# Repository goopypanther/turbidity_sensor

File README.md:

Water Turbidity Sensor Project
==============================

Hackerbot labs would like to place a number of water turbidity sensor packages in dive sites around Puget Sound to provide up-to-date visibility and water temperature information.

The sensor string will be suspended between a weight and small buoy which will contain a battery, solar panels and communication antenna. The installations will be close to shore and will probably use local wifi or a LTE cellular data connection.

Research
--------

[This folder](https://github.com/JeremyRuhland/turbidity_sensor/tree/master/research) contains information and design specs related to the sensor packages and their installation.

Prototypes
----------

[This folder](https://github.com/JeremyRuhland/turbidity_sensor/tree/master/prototypes) contains schematics and code used for prototype systems intented to guide the design of the sensors and their housings.

Designs
-------

[This folder](https://github.com/JeremyRuhland/turbidity_sensor/tree/master/designs) contains possible designs for the production sensor strings.

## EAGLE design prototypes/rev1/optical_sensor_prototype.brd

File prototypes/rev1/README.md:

This prototype is intended to test the behavior of IR LED/photodiode pairs at a variety of angles to narrow down the best method of obtaining measurements of water turbidity (direct opacity measurement/rayleigh scattering).

Each photodiode is connected to a transimpedance amplifier and broken out to a header for oscope/adc conversion. Everything should get wired up and then coated with epoxy so we can dunk it.

Schematic is easily [viewable in pdf form](https://github.com/JeremyRuhland/turbidity_sensor/raw/master/prototypes/rev1/optical_sensor_prototype.pdf)

Calcuations
-----------

Infrared LED current limit:

    3.3V
     |
     R --- 1.69V drop & 70mA = 24.25Ohm @ 118mW
     |
    LED -- 70mA @ 1.6V & 112mW
     |
    FET -- 29mOhm * 70mA = 0.00203V & 142uW
     |
    GND

Photodiode transimpedance amplifier feedback:

Photodiode should have a reverse light current on the order of several microamps, a 10kOhm feedback resistor will amplify this into the range of tens of millivolts.

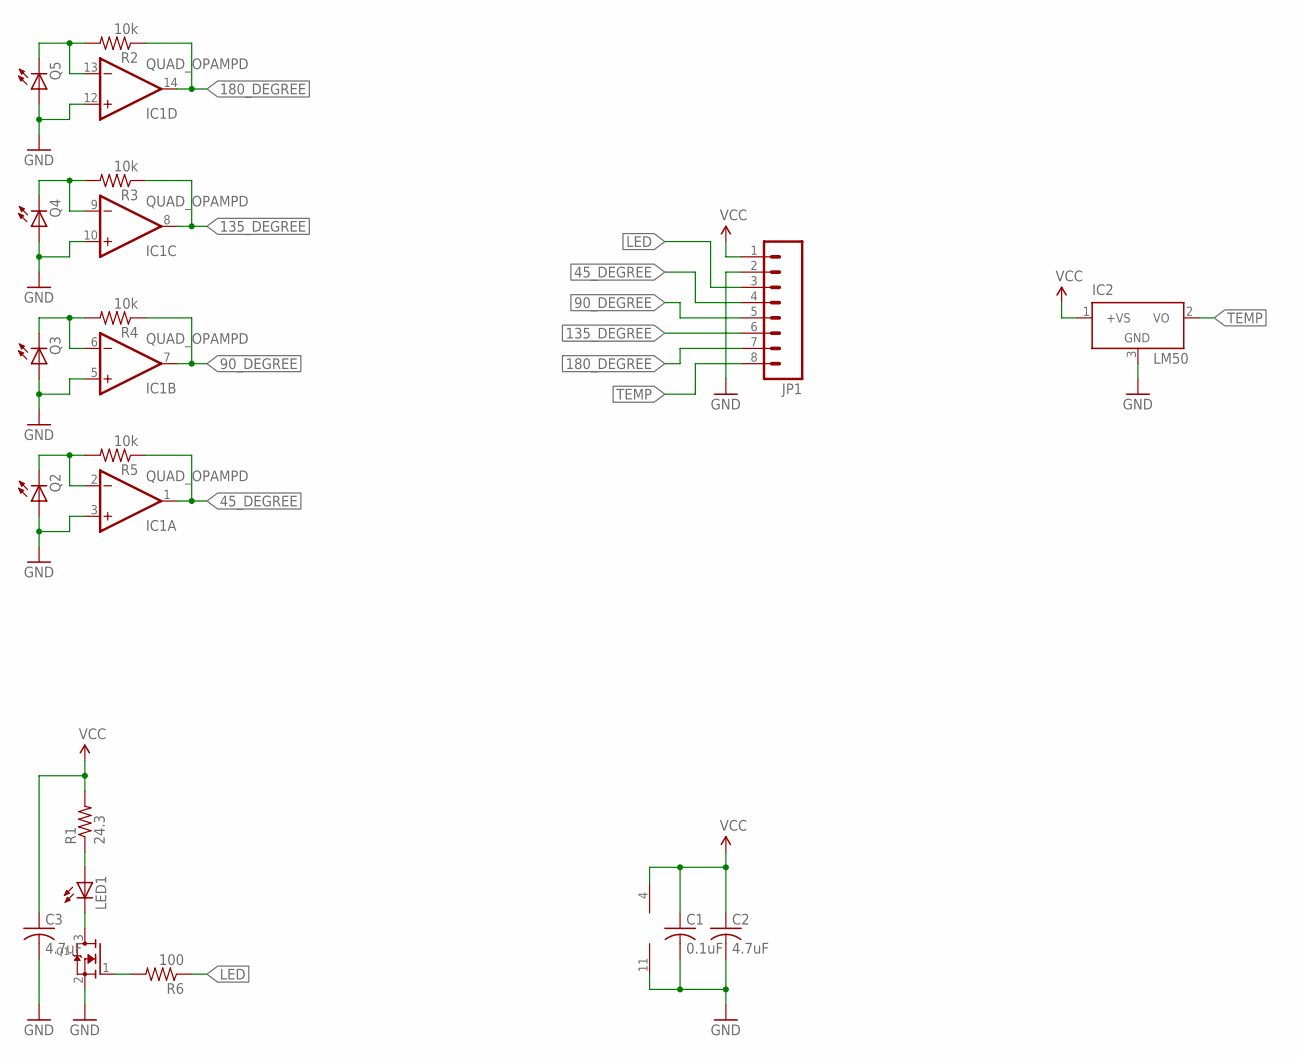
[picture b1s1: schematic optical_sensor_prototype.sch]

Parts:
C1: 0.1uF; C1206
C2, C3: 4.7uF; C1206
IC1: QUAD_OPAMPD; SO14
IC2: LM50; SOT23
JP1: M081X08; 1X08
LED1: LEDSMT1206; 1206
Q1: MOSFET-NREFLOW; SOT23
Q2, Q3, Q4, Q5: LEDSMT1206; 1206
R1: 24.3; R1206
R2, R3, R4, R5: 10k; R1206
R6: 100; R1206

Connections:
45_DEGREE: IC1.1 (OUT), JP1.4, R5.1
90_DEGREE: IC1.7 (OUT), JP1.5, R4.1
135_DEGREE: IC1.8 (OUT), JP1.6, R3.1
180_DEGREE: IC1.14 (OUT), JP1.7, R2.1
GND: C1.2, C2.2, C3.2, IC1.3 (+IN), IC1.5 (+IN), IC1.10 (+IN), IC1.11 (V-), IC1.12 (+IN), IC2.3 (GND), JP1.2, Q1.2 (S), Q2.A, Q3.A, Q4.A, Q5.A
LED: JP1.3, R6.1
unnamed: LED1.A, R1.1
unnamed: IC1.2 (-IN), Q2.C, R5.2
unnamed: LED1.C, Q1.3 (D)
unnamed: Q1.1 (G), R6.2
unnamed: IC1.6 (-IN), Q3.C, R4.2
unnamed: IC1.13 (-IN), Q5.C, R2.2
unnamed: IC1.9 (-IN), Q4.C, R3.2
TEMP: IC2.2 (VO), JP1.8
VCC: C1.1, C2.1, C3.1, IC1.4 (V+), IC2.1 (+VS), JP1.1, R1.2

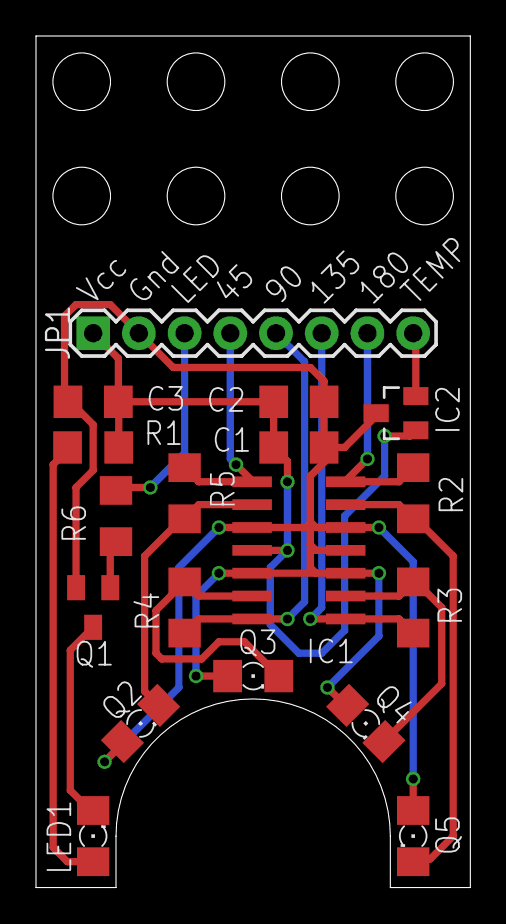
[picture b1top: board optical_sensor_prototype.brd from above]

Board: 2 copper layers, 24.1 x 47.3 mm, 18 parts (0 on the bottom side), 15 nets.

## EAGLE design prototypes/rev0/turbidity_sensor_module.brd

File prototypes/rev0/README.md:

This is an early version of an AVR based LED/photodiode measurement board with a daisy-chainable RS-485 communication bus.

Schematic is easily [viewable in pdf form](https://github.com/JeremyRuhland/turbidity_sensor/raw/master/prototypes/rev0/turbidity_sensor_module.pdf)

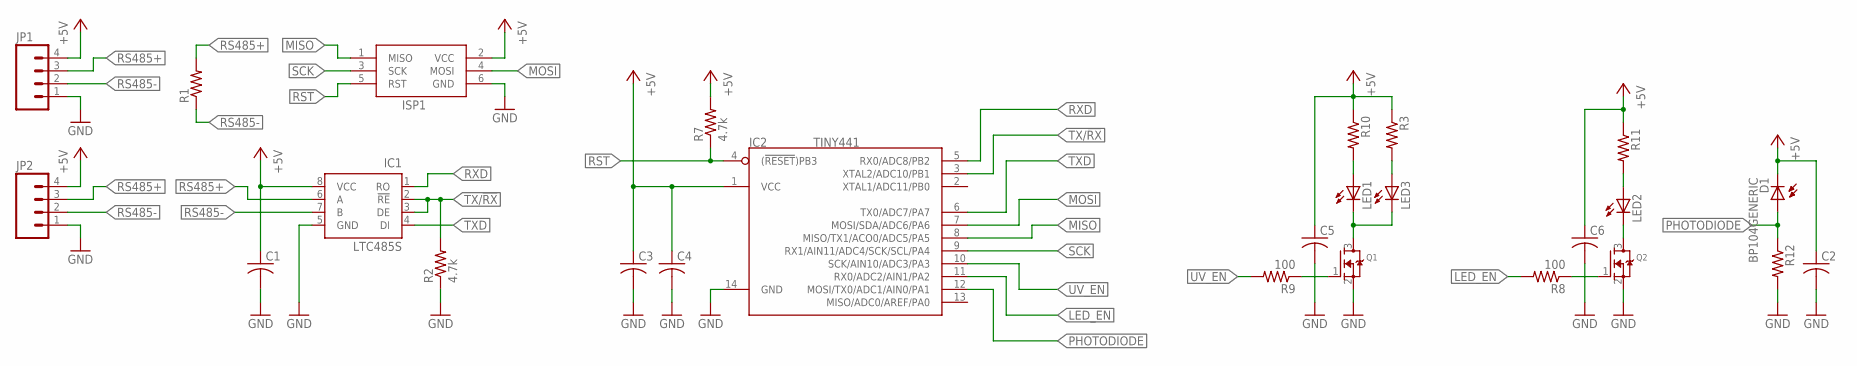
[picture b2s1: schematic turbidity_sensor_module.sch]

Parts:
C1, C2, C3, C4, C5, C6: C-USC1206; C1206
D1: BP104GENERIC; PHOTODIODE
IC1: LTC485S; SOIC8
IC2: TINY441; SOIC14
ISP1: AVRISP-6; AVRISP
JP1, JP2: M04LONGPADS; 1X04_LONGPADS
LED1, LED2, LED3: LED5MM
Q1, Q2: MOSFET-NREFLOW; SOT23
R1, R3, R10, R11, R12: R-US_R1206; R1206
R2, R7: 4.7k; R1206
R8, R9: 100; R1206

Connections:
+5V: C1.1, C2.1, C3.1, C4.1, C5.1, C6.1, D1.K (C), IC1.8 (VCC), IC2.1 (VCC), ISP1.2 (VCC), JP1.4, JP2.4, R3.1, R7.2, R10.1, R11.1
GND: C1.2, C2.2, C3.2, C4.2, C5.2, C6.2, IC1.5 (GND), IC2.14 (GND), ISP1.6 (GND), JP1.1, JP2.1, Q1.2 (S), Q2.2 (S), R2.1, R12.2
LED_EN: IC2.11 (RX0/ADC2/AIN1/PA2), R8.2
MISO: IC2.8 (MISO/TX1/ACO0/ADC5/PA5), ISP1.1 (MISO)
MOSI: IC2.7 (MOSI/SDA/ADC6/PA6), ISP1.4 (MOSI)
unnamed: Q2.1 (G), R8.1
unnamed: Q1.1 (G), R9.1
unnamed: LED1.A, R10.2
unnamed: LED2.A, R11.2
unnamed: LED1.K (C), LED3.K (C), Q1.3 (D)
unnamed: LED2.K (C), Q2.3 (D)
unnamed: LED3.A, R3.2
PHOTODIODE: D1.A, IC2.12 (MOSI/TX0/ADC1/AIN0/PA1), R12.1
RS485+: IC1.6 (A), JP1.3, JP2.3, R1.2
RS485-: IC1.7 (B), JP1.2, JP2.2, R1.1
RST: IC2.4 ((!RESET!)PB3), ISP1.5 (RST), R7.1
RXD: IC1.1 (RO), IC2.5 (RX0/ADC8/PB2)
SCK: IC2.9 (RX1/AIN11/ADC4/SCK/SCL/PA4), ISP1.3 (SCK)
TX/!RX: IC1.2 (!RE), IC1.3 (DE), IC2.3 (XTAL2/ADC10/PB1), R2.2
TXD: IC1.4 (DI), IC2.6 (TX0/ADC7/PA7)
UV_EN: IC2.10 (SCK/AIN10/ADC3/PA3), R9.2

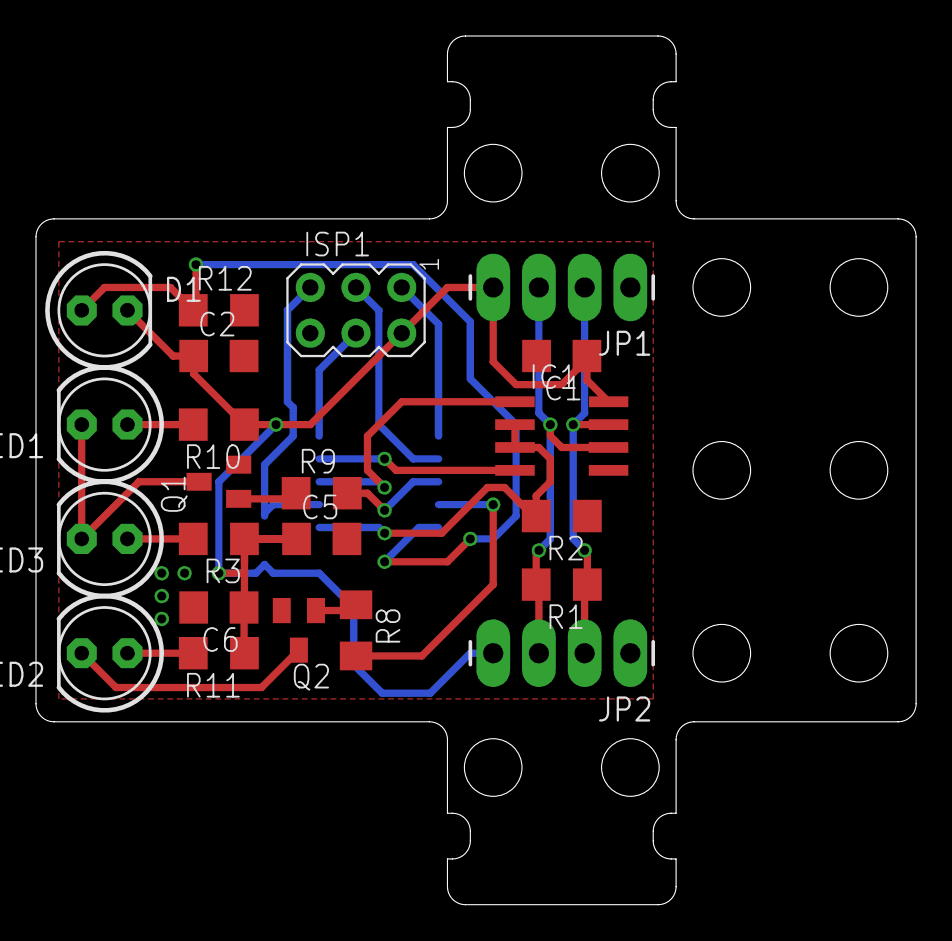
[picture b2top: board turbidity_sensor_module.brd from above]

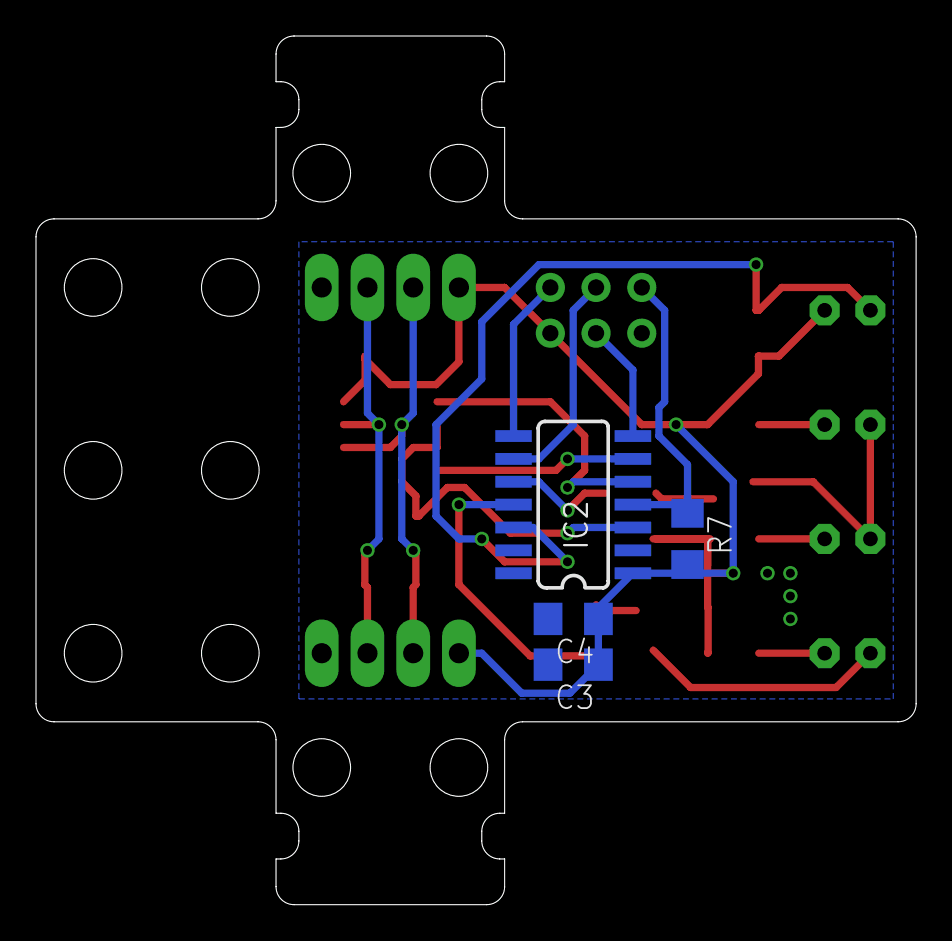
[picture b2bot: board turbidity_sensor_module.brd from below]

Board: 2 copper layers, 48.9 x 48.3 mm, 26 parts (4 on the bottom side), 21 nets.

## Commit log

2014-12-20 current progress on turbidity sensor module
2014-12-28 finishing touches, layed out pcb
2014-12-28 added git ignore
2015-03-06 Added readme
2015-03-06 Put files into new folders
2015-03-06 Started design of prototype optical sensor
2015-03-06 some datasheets for the optical sensor prototype
2015-03-06 fixed image
2015-03-06 added prototype rev1 readme
2015-03-06 added to readme
2015-03-06 Created research readme
2015-03-06 enclosure ideas
2015-03-09 prototype readme file, need to move rev0 here and create rev2
2015-03-09 moved rev0 to prototypes folder
2015-03-09 made readme for rev0
2015-03-10 added system diagram
2015-03-10 slight diagram alteration
2015-03-10 added system diagram image into readme
2015-04-10 Added some calculations into readme
2015-04-10 added remaining component values

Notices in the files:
parts and their libraries:
sparkfun: Licensing: CC v3.0 Share-Alike You are welcome to use this library for commercial purposes.
